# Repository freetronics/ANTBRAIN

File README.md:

AntBrain Robot Controller
==========================
Copyright 2018 Freetronics Pty Ltd  www.freetronics.com  

The AntBrain is a tiny robot controller intended for ant-weight class
combat robots.

It uses the same ATmega328P MCU as the Arduino Uno, and adds 2 H-bridge
motor controllers to drive wheels and a servo output to control a
weapon. A radio control receiver mounts directly onto the board so the
Arduino can read the control signals.

Features:

 * ATmega328P MCU
 * 2 x L9110S H-bridge motor drivers
 * Mount for Flysky radio receiver
 * Servo output

You can view more online at:

  http://www.freetronics.com.au/antbrain

INSTALLATION
------------
The design is saved as an EAGLE project. EAGLE PCB design software is
available from www.cadsoftusa.com free for non-commercial use. To use
this project download it and place the directory containing these files
into the "eagle" directory on your computer. Then open EAGLE and
navigate to the project.

DISTRIBUTION
------------
The specific terms of distribution of this project are governed by the
license referenced below.

LICENSE
-------
Licensed under the TAPR Open Hardware License (www.tapr.org/OHL).
The "license" folder within this repository also contains a copy of
this license in plain text format.

CREDITS
-------
Designed by Jonathan Oxer (jon@freetronics.com)

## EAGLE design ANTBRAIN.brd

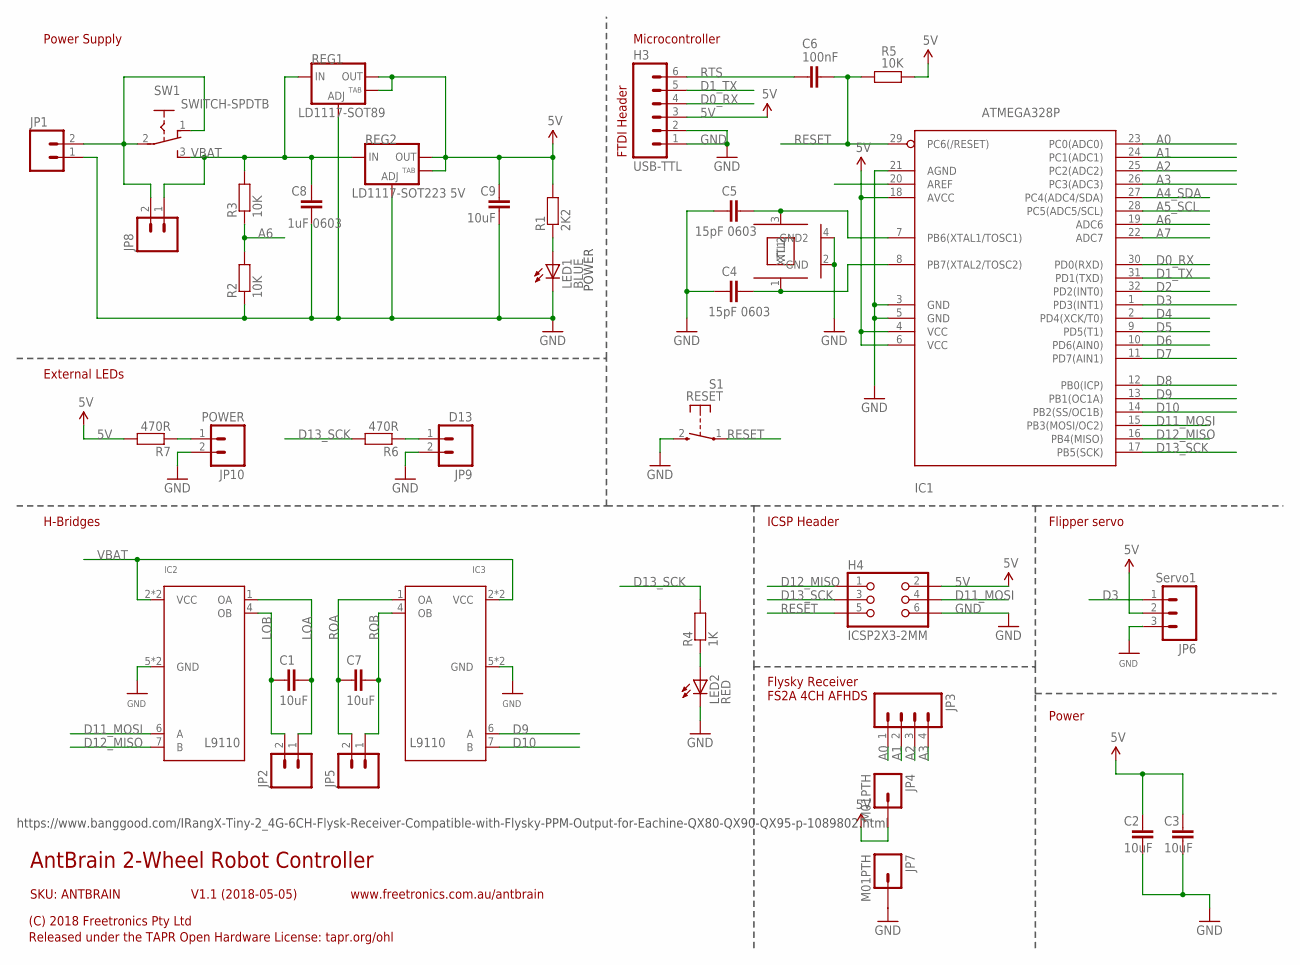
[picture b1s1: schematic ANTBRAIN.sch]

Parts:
C1, C2, C3, C7, C9: 10uF; 0805
C4, C5: 15pF 0603; 0603
C6: 100nF; 0603
C8: 1uF 0603; 0603
H3: USB-TTL; 1X06
H4: ICSP2X3-2MM; M2X3-2MM
IC1: ATMEGA328P; TQFP32-08
IC2, IC3: L9110SO8; SO08
JP1, JP2, JP5: M02PTH; 1X02
JP3: M04PTH; 1X04
JP4, JP7: M01PTH; 1X01
JP6: Servo1; 1X03
JP8: M022MM; M02-2MM
JP9: D13; M02-2MM
JP10: POWER; M02-2MM
LED1: BLUE; LED-0603
LED2: RED; LED-0603
R1: 2K2; 0603
R2, R3, R5: 10K; 0603
R4: 1K; 0603
R6, R7: 470R; 0603
REG1: LD1117-SOT89; SOT89
REG2: LD1117-SOT223 5V; SOT223
S1: RESET; TACTILE_SWITCH_SMD_2PIN_TINY
SW1: SWITCH-SPDTB; SPDT-2.5MM
XTL1: 16MHz; CRYSTAL-SMD-3X2

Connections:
5V: C2.1, C3.1, C9.1, H3.3, H4.2, IC1.4 (VCC), IC1.6 (VCC), IC1.18 (AVCC), JP4.1, JP6.2, R1.2, R5.2, R7.2, REG1.2 (OUT), REG1.4 (OUT), REG2.2 (OUT), REG2.4 (OUT)
A0: IC1.23 (PC0(ADC0)), JP3.1
A1: IC1.24 (PC1(ADC1)), JP3.2
A2: IC1.25 (PC2(ADC2)), JP3.3
A3: IC1.26 (PC3(ADC3)), JP3.4
A4_SDA: IC1.27 (PC4(ADC4/SDA))
A5_SCL: IC1.28 (PC5(ADC5/SCL))
A6: IC1.19 (ADC6), R2.2, R3.1
A7: IC1.22 (ADC7)
AREF: IC1.20 (AREF)
D0_RX: H3.4, IC1.30 (PD0(RXD))
D1_TX: H3.5, IC1.31 (PD1(TXD))
D2: IC1.32 (PD2(INT0))
D3: IC1.1 (PD3(INT1)), JP6.1
D4: IC1.2 (PD4(XCK/T0))
D5: IC1.9 (PD5(T1))
D6: IC1.10 (PD6(AIN0))
D7: IC1.11 (PD7(AIN1))
D8: IC1.12 (PB0(ICP))
D9: IC1.13 (PB1(OC1A)), IC3.6 (A)
D10: IC1.14 (PB2(SS/OC1B)), IC3.7 (B)
D11_MOSI: H4.4, IC1.15 (PB3(MOSI/OC2)), IC2.6 (A)
D12_MISO: H4.1, IC1.16 (PB4(MISO)), IC2.7 (B)
D13_SCK: H4.3, IC1.17 (PB5(SCK)), R4.2, R6.2
GND: C2.2, C3.2, C4.1, C5.1, C8.2, C9.2, H3.1, H3.2, H4.6, IC1.3 (GND), IC1.5 (GND), IC1.21 (AGND), IC2.5 (GND), IC2.8 (GND), IC3.5 (GND), IC3.8 (GND), JP1.1, JP6.3, JP7.1, JP9.2, JP10.2, LED1.C, LED2.C, R2.1, REG1.1 (ADJ), REG2.1 (ADJ), S1.2 (S), XTL1.2 (GND), XTL1.4 (GND2)
LOA: C1.1, IC2.1 (OA), JP2.1
LOB: C1.2, IC2.4 (OB), JP2.2
unnamed: LED2.A, R4.1
unnamed: JP10.1, R7.1
unnamed: JP9.1, R6.1
unnamed: JP1.2, JP8.2, SW1.1, SW1.2
unnamed: C5.2, IC1.7 (PB6(XTAL1/TOSC1)), XTL1.3 (XTL2)
unnamed: C4.2, IC1.8 (PB7(XTAL2/TOSC2)), XTL1.1 (XTL1)
unnamed: LED1.A, R1.1
RESET: C6.2, H4.5, IC1.29 (PC6(/RESET)), R5.1, S1.1
ROA: C7.2, IC3.1 (OA), JP5.2
ROB: C7.1, IC3.4 (OB), JP5.1
RTS: C6.1, H3.6
VBAT: C8.1, IC2.2 (VCC), IC2.3 (VCC), IC3.2 (VCC), IC3.3 (VCC), JP8.1, R3.2, REG1.3 (IN), REG2.3 (IN), SW1.3

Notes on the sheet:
AntBrain 2-Wheel Robot Controller
V1.1 (2018-05-05)
(C) 2018 Freetronics Pty Ltd
Released under the TAPR Open Hardware License: tapr.org/ohl
www.freetronics.com.au/antbrain
SKU: ANTBRAIN
https://www.banggood.com/IRangX-Tiny-2_4G-6CH-Flysk-Receiver-Compatible-with-Flysky-PPM-Output-for-Eachine-QX80-QX90-QX95-p-1089802.html
Power
ICSP Header
Microcontroller
FTDI Header
Flipper servo
POWER
Power Supply
H-Bridges
Flysky Receiver FS2A 4CH AFHDS
External LEDs

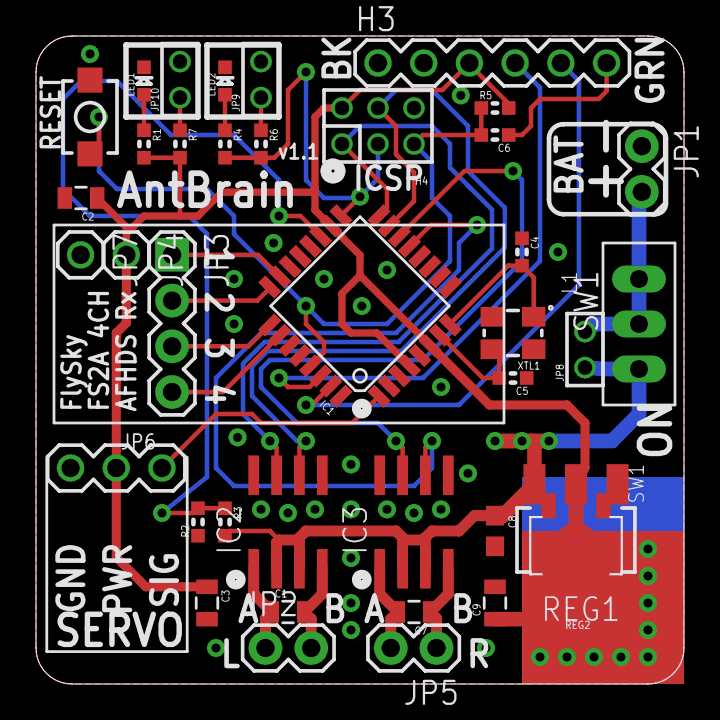
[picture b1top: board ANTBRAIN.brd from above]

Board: 2 copper layers, 36.0 x 36.0 mm, 38 parts (0 on the bottom side), 29 nets.

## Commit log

2018-04-09 Initial project import
2018-04-09 Shrunk board to 36x36mm
2018-04-10 Added license information
2018-04-18 Finished routing for v1.0 release
2018-06-08 Fixed H-Bridge footprints for v1.1 release
2019-04-15 Silkscreen fixes
